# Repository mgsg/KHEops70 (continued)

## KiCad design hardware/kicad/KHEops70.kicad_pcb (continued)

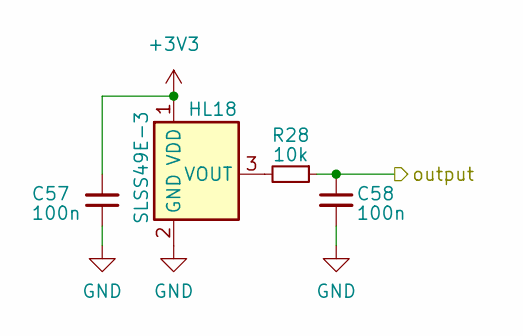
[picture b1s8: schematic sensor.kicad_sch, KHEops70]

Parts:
C57, C58: 100n; C_0805_2012Metric; LCSC C49678
HL18: SLSS49E-3; SLSS49E-3 with MX holes; LCSC C2904393
R28: 10k; R_0805_2012Metric; LCSC C17414

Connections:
+3V3: C57.2, HL18.1 (VDD); also elsewhere on the board
/multiplexers/keys/KEYS_1_5: C58.1, R28.1; also elsewhere on the board
unnamed: HL18.3 (VOUT), R28.2

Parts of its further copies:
C21, C22, C23, C24, C25, C26, C27, C28, C29, C30, C31, C32, C33, C34, C35, C36, C37, C38, C39, C40, C41, C42, C43, C44, C45, C46, C47, C48, C49, C50, C51, C52, C53, C54, C55, C56, C59, C60, C61, C62, C63, C64, C65, C66, C67, C68, C69, C70, C71, C72, C75, C76, C77, C78, C79, C80, C81, C82, C83, C84, C85, C86, C87, C88, C89, C90, C91, C92, C93, C94, C95, C96, C97, C98, C99, C100, C105, C106, C107, C108, C109, C110, C111, C112, C113, C114, C115, C116, C117, C118, C119, C120, C121, C122, C123, C124, C125, C126, C127, C128, C129, C130, C133, C134, C135, C136, C137, C138, C139, C140, C141, C142, C143, C144, C145, C146, C147, C148, C149, C150, C151, C152, C153, C154, C155, C156, C157, C158, C260, C261, C263, C264, C266, C267, C269, C270, C272, C273: 100n; C_0805_2012Metric; LCSC C49678
HL0, HL1, HL2, HL3, HL4, HL5, HL6, HL7, HL8, HL9, HL10, HL11, HL12, HL13, HL14, HL15, HL16, HL17, HL19, HL20, HL21, HL22, HL23, HL24, HL25, HL26, HL27, HL28, HL29, HL30, HL31, HL32, HL33, HL34, HL35, HL36, HL37, HL38, HL39, HL40, HL41, HL42, HL43, HL44, HL45, HL46, HL47, HL48, HL49, HL50, HL51, HL52, HL53, HL54, HL55, HL56, HL57, HL58, HL59, HL60, HL61, HL62, HL63, HL64, HL65, HL66, HL67, HL68, HL69: SLSS49E-3; SLSS49E-3 with MX holes; LCSC C2904393
R10, R11, R12, R13, R14, R15, R16, R17, R18, R19, R20, R21, R22, R23, R24, R25, R26, R27, R29, R30, R31, R32, R33, R34, R35, R37, R38, R39, R40, R41, R42, R43, R44, R45, R46, R47, R48, R49, R52, R53, R54, R55, R56, R57, R58, R59, R60, R61, R62, R63, R64, R66, R67, R68, R69, R70, R71, R72, R73, R74, R75, R76, R77, R78, R79, R80, R81, R82, R83: 10k; R_0805_2012Metric; LCSC C17414

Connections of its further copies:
+3V3: C21.2, C23.2, C25.2, C27.2, C29.2, C31.2, C33.2, C35.2, C37.2, C39.2, C41.2, C43.2, C45.2, C47.2, C49.2, C51.2, C53.2, C55.2, C59.2, C61.2, C63.2, C65.2, C67.2, C69.2, C71.2, C75.2, C77.2, C79.2, C81.2, C83.2, C85.2, C87.2, C89.2, C91.2, C93.2, C95.2, C97.2, C99.2, C105.2, C107.2, C109.2, C111.2, C113.2, C115.2, C117.2, C119.2, C121.2, C123.2, C125.2, C127.2, C129.2, C133.2, C135.2, C137.2, C139.2, C141.2, C143.2, C145.2, C147.2, C149.2, C151.2, C153.2, C155.2, C157.2, C260.2, C263.2, C266.2, C269.2, C272.2, HL0.1 (VDD), HL1.1 (VDD), HL2.1 (VDD), HL3.1 (VDD), HL4.1 (VDD), HL5.1 (VDD), HL6.1 (VDD), HL7.1 (VDD), HL8.1 (VDD), HL9.1 (VDD), HL10.1 (VDD), HL11.1 (VDD), HL12.1 (VDD), HL13.1 (VDD), HL14.1 (VDD), HL15.1 (VDD), HL16.1 (VDD), HL17.1 (VDD), HL19.1 (VDD), HL20.1 (VDD), HL21.1 (VDD), HL22.1 (VDD), HL23.1 (VDD), HL24.1 (VDD), HL25.1 (VDD), HL26.1 (VDD), HL27.1 (VDD), HL28.1 (VDD), HL29.1 (VDD), HL30.1 (VDD), HL31.1 (VDD), HL32.1 (VDD), HL33.1 (VDD), HL34.1 (VDD), HL35.1 (VDD), HL36.1 (VDD), HL37.1 (VDD), HL38.1 (VDD), HL39.1 (VDD), HL40.1 (VDD), HL41.1 (VDD), HL42.1 (VDD), HL43.1 (VDD), HL44.1 (VDD), HL45.1 (VDD), HL46.1 (VDD), HL47.1 (VDD), HL48.1 (VDD), HL49.1 (VDD), HL50.1 (VDD), HL51.1 (VDD), HL52.1 (VDD), HL53.1 (VDD), HL54.1 (VDD), HL55.1 (VDD), HL56.1 (VDD), HL57.1 (VDD), HL58.1 (VDD), HL59.1 (VDD), HL60.1 (VDD), HL61.1 (VDD), HL62.1 (VDD), HL63.1 (VDD), HL64.1 (VDD), HL65.1 (VDD), HL66.1 (VDD), HL67.1 (VDD), HL68.1 (VDD), HL69.1 (VDD); also elsewhere on the board
/multiplexers/keys/KEYS_0_0: C22.1, R10.1; also elsewhere on the board
/multiplexers/keys/KEYS_0_1: C24.1, R11.1; also elsewhere on the board
/multiplexers/keys/KEYS_0_4: C30.1, R14.1; also elsewhere on the board
/multiplexers/keys/KEYS_0_5: C32.1, R15.1; also elsewhere on the board
/multiplexers/keys/KEYS_0_6: C34.1, R16.1; also elsewhere on the board
/multiplexers/keys/KEYS_0_7: C36.1, R17.1; also elsewhere on the board
/multiplexers/keys/KEYS_0_8: C38.1, R18.1; also elsewhere on the board
/multiplexers/keys/KEYS_0_9: C40.1, R19.1; also elsewhere on the board
/multiplexers/keys/KEYS_0_10: C42.1, R20.1; also elsewhere on the board
/multiplexers/keys/KEYS_0_11: C44.1, R21.1; also elsewhere on the board
/multiplexers/keys/KEYS_0_12: C46.1, R22.1; also elsewhere on the board
/multiplexers/keys/KEYS_1_0: C48.1, R23.1; also elsewhere on the board
/multiplexers/keys/KEYS_1_1: C50.1, R24.1; also elsewhere on the board
/multiplexers/keys/KEYS_1_4: C56.1, R27.1; also elsewhere on the board
/multiplexers/keys/KEYS_1_6: C60.1, R29.1; also elsewhere on the board
/multiplexers/keys/KEYS_1_7: C62.1, R30.1; also elsewhere on the board
/multiplexers/keys/KEYS_1_8: C64.1, R31.1; also elsewhere on the board
/multiplexers/keys/KEYS_1_9: C66.1, R32.1; also elsewhere on the board
/multiplexers/keys/KEYS_1_10: C68.1, R33.1; also elsewhere on the board
/multiplexers/keys/KEYS_1_11: C70.1, R34.1; also elsewhere on the board
/multiplexers/keys/KEYS_1_12: C72.1, R35.1; also elsewhere on the board
/multiplexers/keys/KEYS_2_0: C76.1, R37.1; also elsewhere on the board
/multiplexers/keys/KEYS_2_1: C78.1, R38.1; also elsewhere on the board
/multiplexers/keys/KEYS_2_4: C84.1, R41.1; also elsewhere on the board
/multiplexers/keys/KEYS_2_5: C86.1, R42.1; also elsewhere on the board
/multiplexers/keys/KEYS_2_6: C88.1, R43.1; also elsewhere on the board
/multiplexers/keys/KEYS_2_7: C90.1, R44.1; also elsewhere on the board
/multiplexers/keys/KEYS_2_8: C92.1, R45.1; also elsewhere on the board
/multiplexers/keys/KEYS_2_9: C94.1, R46.1; also elsewhere on the board
/multiplexers/keys/KEYS_2_10: C96.1, R47.1; also elsewhere on the board
/multiplexers/keys/KEYS_2_11: C98.1, R48.1; also elsewhere on the board
/multiplexers/keys/KEYS_2_12: C100.1, R49.1; also elsewhere on the board
/multiplexers/keys/KEYS_2_13: C273.1, R83.1; also elsewhere on the board
/multiplexers/keys/KEYS_3_0: C106.1, R52.1; also elsewhere on the board
/multiplexers/keys/KEYS_3_1: C108.1, R53.1; also elsewhere on the board
/multiplexers/keys/KEYS_3_2: C110.1, R54.1; also elsewhere on the board
/multiplexers/keys/KEYS_3_3: C112.1, R55.1; also elsewhere on the board
/multiplexers/keys/KEYS_3_4: C114.1, R56.1; also elsewhere on the board
/multiplexers/keys/KEYS_3_5: C116.1, R57.1; also elsewhere on the board
/multiplexers/keys/KEYS_3_6: C118.1, R58.1; also elsewhere on the board
/multiplexers/keys/KEYS_3_7: C120.1, R59.1; also elsewhere on the board
/multiplexers/keys/KEYS_3_8: C122.1, R60.1; also elsewhere on the board
/multiplexers/keys/KEYS_3_9: C124.1, R61.1; also elsewhere on the board
/multiplexers/keys/KEYS_3_10: C126.1, R62.1; also elsewhere on the board
/multiplexers/keys/KEYS_3_11: C128.1, R63.1; also elsewhere on the board
/multiplexers/keys/KEYS_3_12: C130.1, R64.1; also elsewhere on the board
/multiplexers/keys/KEYS_3_13: C261.1, R80.1; also elsewhere on the board
/multiplexers/keys/KEYS_3_14: C264.1, R79.1; also elsewhere on the board
/multiplexers/keys/KEYS_4_0: C134.1, R66.1; also elsewhere on the board
/multiplexers/keys/KEYS_4_1: C136.1, R67.1; also elsewhere on the board
/multiplexers/keys/KEYS_4_2: C138.1, R68.1; also elsewhere on the board
/multiplexers/keys/KEYS_4_3: C140.1, R69.1; also elsewhere on the board
/multiplexers/keys/KEYS_4_4: C142.1, R70.1; also elsewhere on the board
/multiplexers/keys/KEYS_4_5: C144.1, R71.1; also elsewhere on the board
/multiplexers/keys/KEYS_4_6: C146.1, R72.1; also elsewhere on the board
/multiplexers/keys/KEYS_4_7: C148.1, R73.1; also elsewhere on the board
/multiplexers/keys/KEYS_4_8: C150.1, R74.1; also elsewhere on the board
/multiplexers/keys/KEYS_4_9: C152.1, R75.1; also elsewhere on the board
/multiplexers/keys/KEYS_4_10: C154.1, R76.1; also elsewhere on the board
/multiplexers/keys/KEYS_4_11: C156.1, R77.1; also elsewhere on the board
/multiplexers/keys/KEYS_4_12: C158.1, R78.1; also elsewhere on the board
/multiplexers/keys/KEYS_4_13: C267.1, R81.1; also elsewhere on the board
/multiplexers/keys/KEYS_4_14: C270.1, R82.1; also elsewhere on the board
unnamed: HL0.3 (VOUT), R10.2
unnamed: HL1.3 (VOUT), R11.2
unnamed: HL2.3 (VOUT), R12.2
unnamed: HL3.3 (VOUT), R13.2
unnamed: HL4.3 (VOUT), R14.2
unnamed: HL5.3 (VOUT), R15.2
unnamed: HL6.3 (VOUT), R16.2
unnamed: HL7.3 (VOUT), R17.2
unnamed: HL8.3 (VOUT), R18.2
unnamed: HL9.3 (VOUT), R19.2
unnamed: HL10.3 (VOUT), R20.2
unnamed: HL11.3 (VOUT), R21.2
unnamed: HL12.3 (VOUT), R22.2
unnamed: HL13.3 (VOUT), R23.2
unnamed: HL14.3 (VOUT), R24.2
unnamed: HL15.3 (VOUT), R25.2
unnamed: HL16.3 (VOUT), R26.2
unnamed: HL17.3 (VOUT), R27.2
unnamed: HL19.3 (VOUT), R29.2
unnamed: HL20.3 (VOUT), R30.2
unnamed: HL21.3 (VOUT), R31.2
unnamed: HL22.3 (VOUT), R32.2
unnamed: HL23.3 (VOUT), R33.2
unnamed: HL24.3 (VOUT), R34.2
unnamed: HL25.3 (VOUT), R35.2
unnamed: HL26.3 (VOUT), R37.2
unnamed: HL27.3 (VOUT), R38.2
unnamed: HL28.3 (VOUT), R39.2
unnamed: HL29.3 (VOUT), R40.2
unnamed: HL30.3 (VOUT), R41.2
unnamed: HL31.3 (VOUT), R42.2
unnamed: HL32.3 (VOUT), R43.2
unnamed: HL33.3 (VOUT), R44.2
unnamed: HL34.3 (VOUT), R45.2
unnamed: HL35.3 (VOUT), R46.2
unnamed: HL36.3 (VOUT), R47.2
unnamed: HL37.3 (VOUT), R48.2
unnamed: HL38.3 (VOUT), R49.2
unnamed: HL39.3 (VOUT), R83.2
unnamed: HL40.3 (VOUT), R52.2
unnamed: HL41.3 (VOUT), R53.2
unnamed: HL42.3 (VOUT), R54.2
unnamed: HL43.3 (VOUT), R55.2
unnamed: HL44.3 (VOUT), R56.2
unnamed: HL45.3 (VOUT), R57.2
unnamed: HL46.3 (VOUT), R58.2
unnamed: HL47.3 (VOUT), R59.2
unnamed: HL48.3 (VOUT), R60.2
unnamed: HL49.3 (VOUT), R61.2
unnamed: HL50.3 (VOUT), R62.2
unnamed: HL51.3 (VOUT), R63.2
unnamed: HL52.3 (VOUT), R64.2
unnamed: HL53.3 (VOUT), R80.2
unnamed: HL54.3 (VOUT), R79.2
unnamed: HL55.3 (VOUT), R66.2
unnamed: HL56.3 (VOUT), R67.2
unnamed: HL57.3 (VOUT), R68.2
unnamed: HL58.3 (VOUT), R69.2
unnamed: HL59.3 (VOUT), R70.2
unnamed: HL60.3 (VOUT), R71.2
unnamed: HL61.3 (VOUT), R72.2
unnamed: HL62.3 (VOUT), R73.2
unnamed: HL63.3 (VOUT), R74.2
unnamed: HL64.3 (VOUT), R75.2
unnamed: HL65.3 (VOUT), R76.2
unnamed: HL66.3 (VOUT), R77.2
unnamed: HL67.3 (VOUT), R78.2
unnamed: HL68.3 (VOUT), R81.2
unnamed: HL69.3 (VOUT), R82.2

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
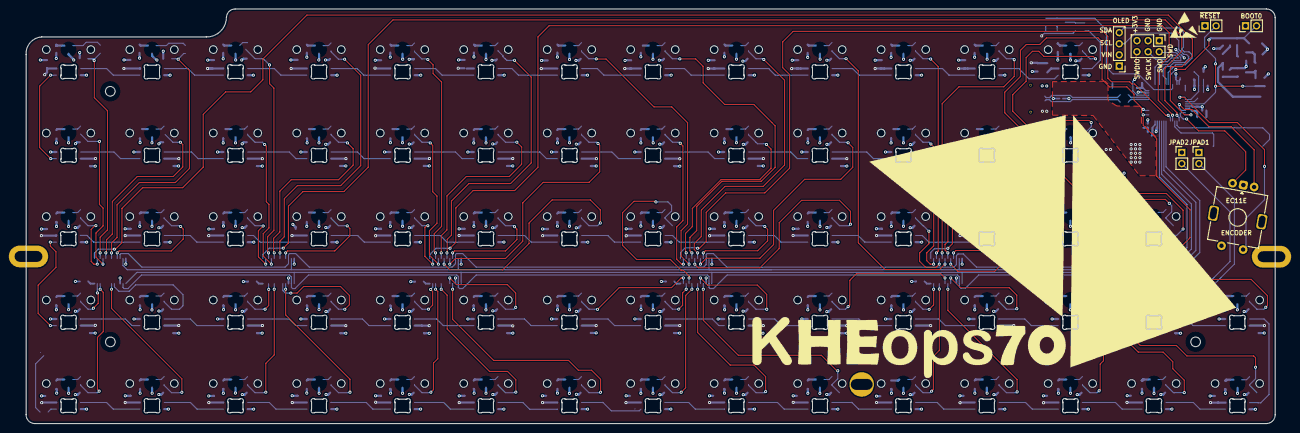
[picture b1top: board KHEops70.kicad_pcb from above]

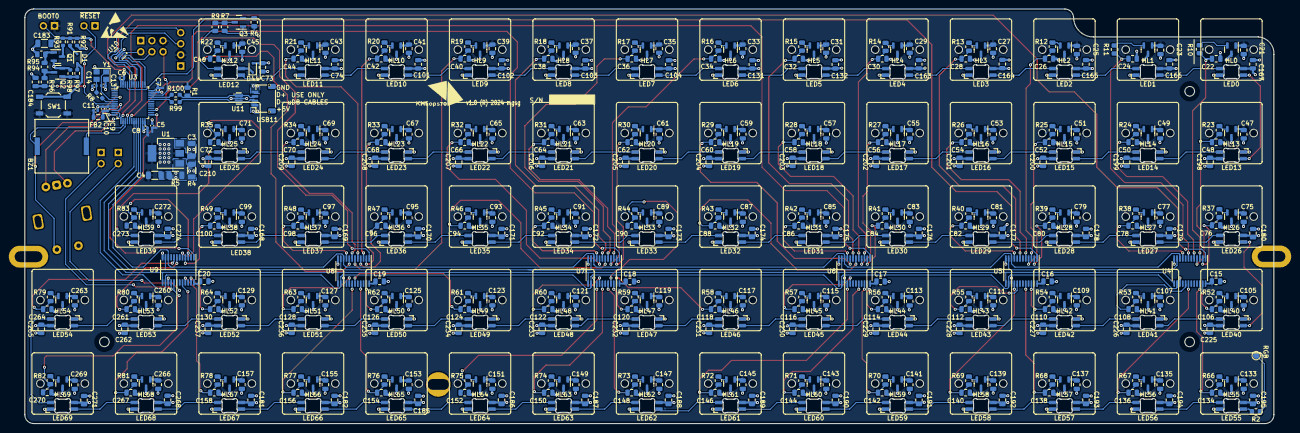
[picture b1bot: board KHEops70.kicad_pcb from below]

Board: 4 copper layers, 285.0 x 94.6 mm, 495 parts (480 on the bottom side), 258 nets.

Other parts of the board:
REF-Antistatic-Logo-Back: ESD-Logo_6.6x6mm_SilkScreen
REF-Antistatic-Logo-Front: ESD-Logo_6.6x6mm_SilkScreen
REF-KHEops70-logo-back: LOGO; KHEops70-logo-m

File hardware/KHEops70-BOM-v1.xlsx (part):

Comment | Designator | Footprint | JLCPCB Part #（optional）
r95 | BZ1 | Buzzer_Beeper:Buzzer_Murata_PKLCS1212E
PAD 1 Header | JPAD1 | Connector_PinHeader_2.54mm:PinHeader_1x02_P2.54mm_Vertical
PAD 2 Header | JPAD2 | Connector_PinHeader_2.54mm:PinHeader_1x02_P2.54mm_Vertical
RGB_DATA_OUT | TP1 | TestPoint:TestPoint_Pad_D1.5mm
STM32F303CBTx | U3 | Package_QFP:LQFP-48_7x7mm_P0.5mm | C108516
10u | C3 | Capacitor_SMD:C_1206_3216Metric | C13585
10u | C183 | Capacitor_SMD:C_1206_3216Metric | C13585
100u | C4 | Capacitor_SMD:C_1206_3216Metric | C15008
100n | C6 | Capacitor_SMD:C_0402_1005Metric | C1525
100n | C7 | Capacitor_SMD:C_0402_1005Metric | C1525
100n | C8 | Capacitor_SMD:C_0402_1005Metric | C1525
100n | C9 | Capacitor_SMD:C_0402_1005Metric | C1525
SM04B-SRSS-TB | USB11 | Connector_JST:JST_SH_SM04B-SRSS-TB_1x04-1MP_P1.00mm_Horizontal | C160404
10k | R93 | Resistor_SMD:R_0603_1608Metric | C17414
10k | R98 | Resistor_SMD:R_0603_1608Metric | C17414
10k | R6 | Resistor_SMD:R_0805_2012Metric | C17414
10k | R10 | Resistor_SMD:R_0805_2012Metric | C17414
10k | R11 | Resistor_SMD:R_0805_2012Metric | C17414
10k | R12 | Resistor_SMD:R_0805_2012Metric | C17414
10k | R13 | Resistor_SMD:R_0805_2012Metric | C17414
10k | R14 | Resistor_SMD:R_0805_2012Metric | C17414
10k | R15 | Resistor_SMD:R_0805_2012Metric | C17414
10k | R16 | Resistor_SMD:R_0805_2012Metric | C17414
10k | R17 | Resistor_SMD:R_0805_2012Metric | C17414
10k | R18 | Resistor_SMD:R_0805_2012Metric | C17414
10k | R19 | Resistor_SMD:R_0805_2012Metric | C17414
10k | R20 | Resistor_SMD:R_0805_2012Metric | C17414
10k | R21 | Resistor_SMD:R_0805_2012Metric | C17414
10k | R22 | Resistor_SMD:R_0805_2012Metric | C17414
10k | R23 | Resistor_SMD:R_0805_2012Metric | C17414
10k | R24 | Resistor_SMD:R_0805_2012Metric | C17414
10k | R25 | Resistor_SMD:R_0805_2012Metric | C17414
10k | R26 | Resistor_SMD:R_0805_2012Metric | C17414
10k | R27 | Resistor_SMD:R_0805_2012Metric | C17414
10k | R28 | Resistor_SMD:R_0805_2012Metric | C17414
10k | R29 | Resistor_SMD:R_0805_2012Metric | C17414
10k | R30 | Resistor_SMD:R_0805_2012Metric | C17414
10k | R31 | Resistor_SMD:R_0805_2012Metric | C17414
10k | R32 | Resistor_SMD:R_0805_2012Metric | C17414
10k | R33 | Resistor_SMD:R_0805_2012Metric | C17414
10k | R34 | Resistor_SMD:R_0805_2012Metric | C17414
10k | R35 | Resistor_SMD:R_0805_2012Metric | C17414
10k | R37 | Resistor_SMD:R_0805_2012Metric | C17414
10k | R38 | Resistor_SMD:R_0805_2012Metric | C17414
10k | R39 | Resistor_SMD:R_0805_2012Metric | C17414
10k | R40 | Resistor_SMD:R_0805_2012Metric | C17414
10k | R41 | Resistor_SMD:R_0805_2012Metric | C17414
10k | R42 | Resistor_SMD:R_0805_2012Metric | C17414
10k | R43 | Resistor_SMD:R_0805_2012Metric | C17414
10k | R44 | Resistor_SMD:R_0805_2012Metric | C17414
10k | R45 | Resistor_SMD:R_0805_2012Metric | C17414
10k | R46 | Resistor_SMD:R_0805_2012Metric | C17414
10k | R47 | Resistor_SMD:R_0805_2012Metric | C17414
10k | R48 | Resistor_SMD:R_0805_2012Metric | C17414
10k | R49 | Resistor_SMD:R_0805_2012Metric | C17414
10k | R52 | Resistor_SMD:R_0805_2012Metric | C17414
10k | R53 | Resistor_SMD:R_0805_2012Metric | C17414
10k | R54 | Resistor_SMD:R_0805_2012Metric | C17414
10k | R55 | Resistor_SMD:R_0805_2012Metric | C17414
10k | R56 | Resistor_SMD:R_0805_2012Metric | C17414
10k | R57 | Resistor_SMD:R_0805_2012Metric | C17414
10k | R58 | Resistor_SMD:R_0805_2012Metric | C17414
10k | R59 | Resistor_SMD:R_0805_2012Metric | C17414
10k | R60 | Resistor_SMD:R_0805_2012Metric | C17414
10k | R61 | Resistor_SMD:R_0805_2012Metric | C17414
10k | R62 | Resistor_SMD:R_0805_2012Metric | C17414
10k | R63 | Resistor_SMD:R_0805_2012Metric | C17414
10k | R64 | Resistor_SMD:R_0805_2012Metric | C17414
10k | R66 | Resistor_SMD:R_0805_2012Metric | C17414
10k | R67 | Resistor_SMD:R_0805_2012Metric | C17414
10k | R68 | Resistor_SMD:R_0805_2012Metric | C17414
10k | R69 | Resistor_SMD:R_0805_2012Metric | C17414
10k | R70 | Resistor_SMD:R_0805_2012Metric | C17414
10k | R71 | Resistor_SMD:R_0805_2012Metric | C17414
10k | R72 | Resistor_SMD:R_0805_2012Metric | C17414
10k | R73 | Resistor_SMD:R_0805_2012Metric | C17414
10k | R74 | Resistor_SMD:R_0805_2012Metric | C17414
10k | R75 | Resistor_SMD:R_0805_2012Metric | C17414
10k | R76 | Resistor_SMD:R_0805_2012Metric | C17414
10k | R77 | Resistor_SMD:R_0805_2012Metric | C17414
10k | R78 | Resistor_SMD:R_0805_2012Metric | C17414
10k | R79 | Resistor_SMD:R_0805_2012Metric | C17414
10k | R80 | Resistor_SMD:R_0805_2012Metric | C17414
10k | R81 | Resistor_SMD:R_0805_2012Metric | C17414
10k | R82 | Resistor_SMD:R_0805_2012Metric | C17414
10k | R83 | Resistor_SMD:R_0805_2012Metric | C17414
10k | R94 | Resistor_SMD:R_0805_2012Metric | C17414
1k | R7 | Resistor_SMD:R_0805_2012Metric | C17513
1 | R4 | Resistor_SMD:R_1206_3216Metric | C17928
1 | R5 | Resistor_SMD:R_1206_3216Metric | C17928
74HC4067 | U4 | Package_SO:TSSOP-24_4.4x7.8mm_P0.65mm | C179326
74HC4067 | U5 | Package_SO:TSSOP-24_4.4x7.8mm_P0.65mm | C179326
74HC4067 | U6 | Package_SO:TSSOP-24_4.4x7.8mm_P0.65mm | C179326
74HC4067 | U7 | Package_SO:TSSOP-24_4.4x7.8mm_P0.65mm | C179326
74HC4067 | U8 | Package_SO:TSSOP-24_4.4x7.8mm_P0.65mm | C179326
74HC4067 | U9 | Package_SO:TSSOP-24_4.4x7.8mm_P0.65mm | C179326
H5VU25U | U10 | MoonBoard:DFN2510 | C20615800
H5VU25U | U11 | MoonBoard:DFN2510 | C20615800
0 | R8 | Resistor_SMD:R_0603_1608Metric_Pad0.98x0.95mm_HandSolder | C21189
0 | R99 | Resistor_SMD:R_0603_1608Metric_Pad0.98x0.95mm_HandSolder | C21189
0 | R100 | Resistor_SMD:R_0603_1608Metric_Pad0.98x0.95mm_HandSolder | C21189
1k | R97 | Resistor_SMD:R_0603_1608Metric | C21190
1N4148WS | D1 | Diode_SMD:D_SOD-323 | C2128
1N4148WS | D44 | Diode_SMD:D_SOD-323 | C2128
1M | R92 | Resistor_SMD:R_0603_1608Metric | C22935
330k | R91 | Resistor_SMD:R_0603_1608Metric | C23137
4u7 | C5 | Capacitor_SMD:C_0402_1005Metric | C23733
100 | R96 | Resistor_SMD:R_0805_2012Metric | C25076
470R | R2 | Resistor_SMD:R_0805_2012Metric | C25117
470 | R9 | Resistor_SMD:R_0805_2012Metric | C25117
100k | R95 | Resistor_SMD:R_0805_2012Metric | C25741
1k5 | R1 | Resistor_SMD:R_0805_2012Metric | C25867
SW_SPST | SW1 | Button_Switch_SMD:SW_SPST_TL3342 | C2886897
SLSS49E-3 | HL0 | MoonBoard:SLSS49E-3 with MX holes | C2904393
SLSS49E-3 | HL1 | MoonBoard:SLSS49E-3 with MX holes | C2904393
SLSS49E-3 | HL2 | MoonBoard:SLSS49E-3 with MX holes | C2904393
SLSS49E-3 | HL3 | MoonBoard:SLSS49E-3 with MX holes | C2904393
SLSS49E-3 | HL4 | MoonBoard:SLSS49E-3 with MX holes | C2904393
SLSS49E-3 | HL5 | MoonBoard:SLSS49E-3 with MX holes | C2904393
SLSS49E-3 | HL6 | MoonBoard:SLSS49E-3 with MX holes | C2904393
SLSS49E-3 | HL7 | MoonBoard:SLSS49E-3 with MX holes | C2904393
SLSS49E-3 | HL8 | MoonBoard:SLSS49E-3 with MX holes | C2904393
SLSS49E-3 | HL9 | MoonBoard:SLSS49E-3 with MX holes | C2904393
SLSS49E-3 | HL10 | MoonBoard:SLSS49E-3 with MX holes | C2904393
SLSS49E-3 | HL11 | MoonBoard:SLSS49E-3 with MX holes | C2904393
SLSS49E-3 | HL12 | MoonBoard:SLSS49E-3 with MX holes | C2904393
SLSS49E-3 | HL13 | MoonBoard:SLSS49E-3 with MX holes | C2904393
SLSS49E-3 | HL14 | MoonBoard:SLSS49E-3 with MX holes | C2904393
SLSS49E-3 | HL15 | MoonBoard:SLSS49E-3 with MX holes | C2904393
SLSS49E-3 | HL16 | MoonBoard:SLSS49E-3 with MX holes | C2904393
SLSS49E-3 | HL17 | MoonBoard:SLSS49E-3 with MX holes | C2904393
SLSS49E-3 | HL18 | MoonBoard:SLSS49E-3 with MX holes | C2904393
SLSS49E-3 | HL19 | MoonBoard:SLSS49E-3 with MX holes | C2904393
SLSS49E-3 | HL20 | MoonBoard:SLSS49E-3 with MX holes | C2904393
SLSS49E-3 | HL21 | MoonBoard:SLSS49E-3 with MX holes | C2904393
SLSS49E-3 | HL22 | MoonBoard:SLSS49E-3 with MX holes | C2904393
SLSS49E-3 | HL23 | MoonBoard:SLSS49E-3 with MX holes | C2904393
SLSS49E-3 | HL24 | MoonBoard:SLSS49E-3 with MX holes | C2904393
SLSS49E-3 | HL25 | MoonBoard:SLSS49E-3 with MX holes | C2904393
SLSS49E-3 | HL26 | MoonBoard:SLSS49E-3 with MX holes | C2904393
SLSS49E-3 | HL27 | MoonBoard:SLSS49E-3 with MX holes | C2904393
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
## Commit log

2026-02-05 v1.0
2026-02-05 Minor changes
2026-02-05 Kicad files uploaded
2026-02-17 Add Ko-fi username for funding support
2026-04-01 cleanup
